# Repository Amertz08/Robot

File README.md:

# Senior design project

Repo for senior design

## Documentation

- [Contribution Guide](CONTRIBUTING.md)
- [Meeting notes](MEETING.md)

## Gantt Chart

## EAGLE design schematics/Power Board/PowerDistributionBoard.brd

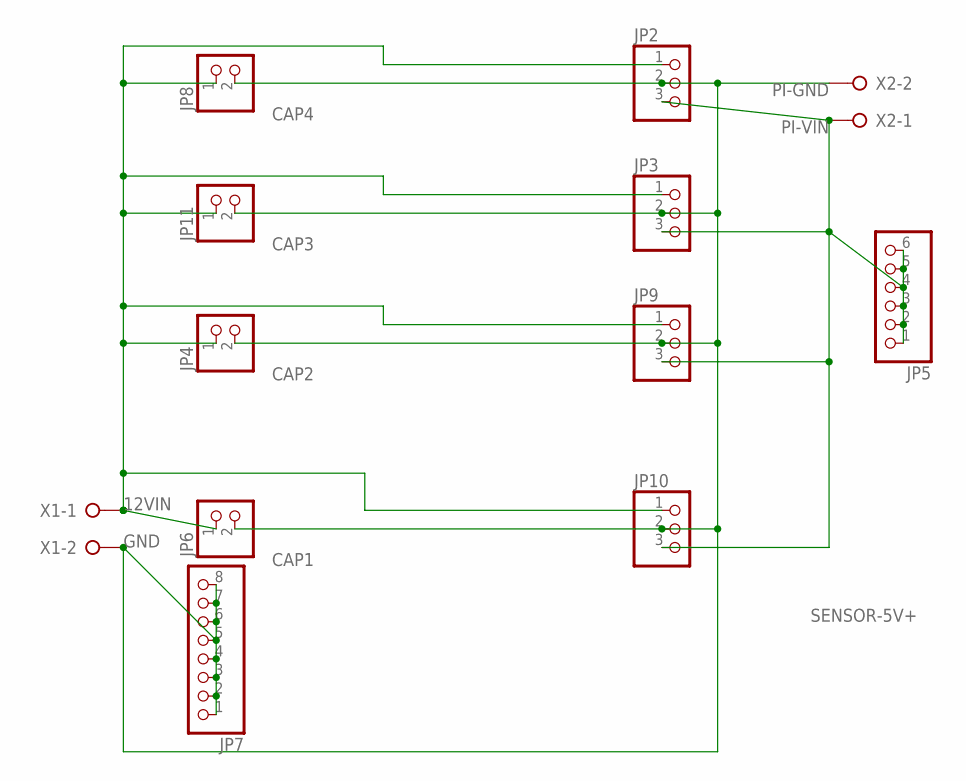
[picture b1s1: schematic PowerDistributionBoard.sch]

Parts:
JP2, JP3, JP9, JP10: PINHD-1X3; 1X03
JP4, JP6, JP8, JP11: PINHD-1X2; 1X02
JP5: PINHD-1X6; 1X06
JP7: PINHD-1X8; 1X08
X1, X2: W237-02P; W237-132

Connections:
COMMON-GND: JP2.2, JP3.2, JP4.2, JP6.2, JP7.1, JP7.2, JP7.3, JP7.4, JP7.5, JP7.6, JP7.7, JP7.8, JP8.2, JP9.2, JP10.2, JP11.2, X1.2, X2.2
unnamed: JP2.1, JP3.1, JP4.1, JP6.1, JP8.1, JP9.1, JP10.1, JP11.1, X1.1
SENSOR-5V+: JP2.3, JP3.3, JP5.1, JP5.2, JP5.3, JP5.4, JP5.5, JP5.6, JP9.3, JP10.3, X2.1

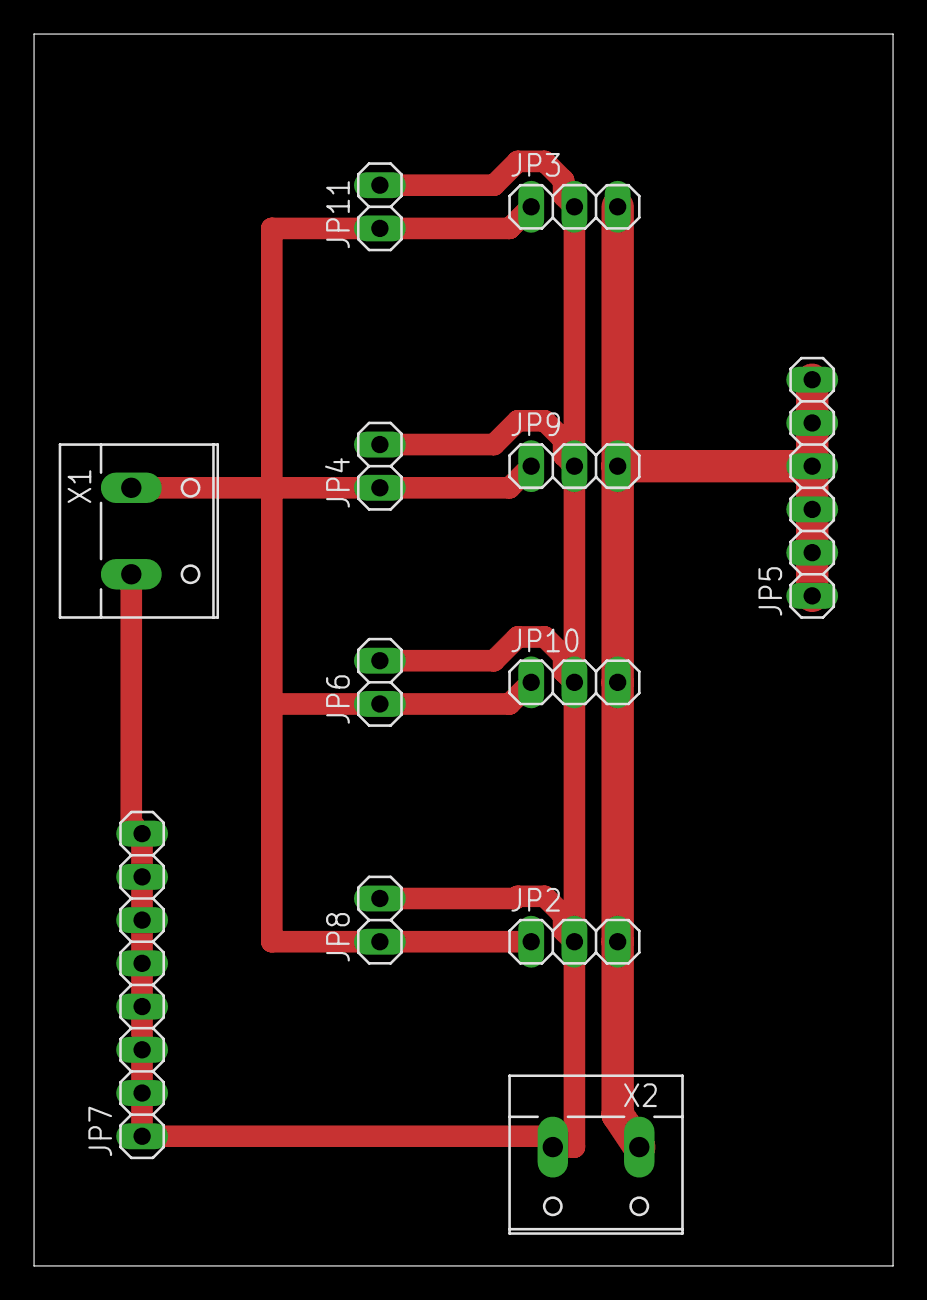
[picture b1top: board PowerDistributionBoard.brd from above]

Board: 2 copper layers, 50.5 x 72.4 mm, 12 parts (0 on the bottom side), 3 nets.

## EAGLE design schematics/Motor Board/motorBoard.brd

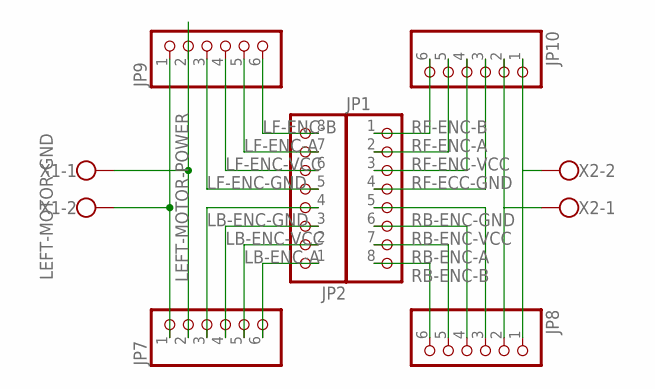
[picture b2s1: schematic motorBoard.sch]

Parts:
JP1, JP2: PINHD-1X8; 1X08
JP7, JP8, JP9, JP10: PINHD-1X6; 1X06
X1, X2: W237-102

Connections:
LB-ENC-A: JP2.2, JP7.5
LB-ENC-B: JP2.1, JP7.6
LB-ENC-GND: JP2.4, JP7.3
LB-ENC-VCC: JP2.3, JP7.4
LEFT-MOTOR-GND: JP7.2, JP9.2, X1.1
LEFT-MOTOR-POWER: JP7.1, JP9.1, X1.2
LF-ENC-A: JP2.7, JP9.5
LF-ENC-B: JP2.8, JP9.6
LF-ENC-GND: JP2.5, JP9.3
LF-ENC-VCC: JP2.6, JP9.4
unnamed: JP8.1, JP10.1, X2.2
unnamed: JP8.2, JP10.2, X2.1
RB-ENC-A: JP1.7, JP8.5
RB-ENC-B: JP1.8, JP8.6
RB-ENC-GND: JP1.5, JP8.3
RB-ENC-VCC: JP1.6, JP8.4
RF-ECC-GND: JP1.4, JP10.3
RF-ENC-A: JP1.2, JP10.5
RF-ENC-B: JP1.1, JP10.6
RF-ENC-VCC: JP1.3, JP10.4

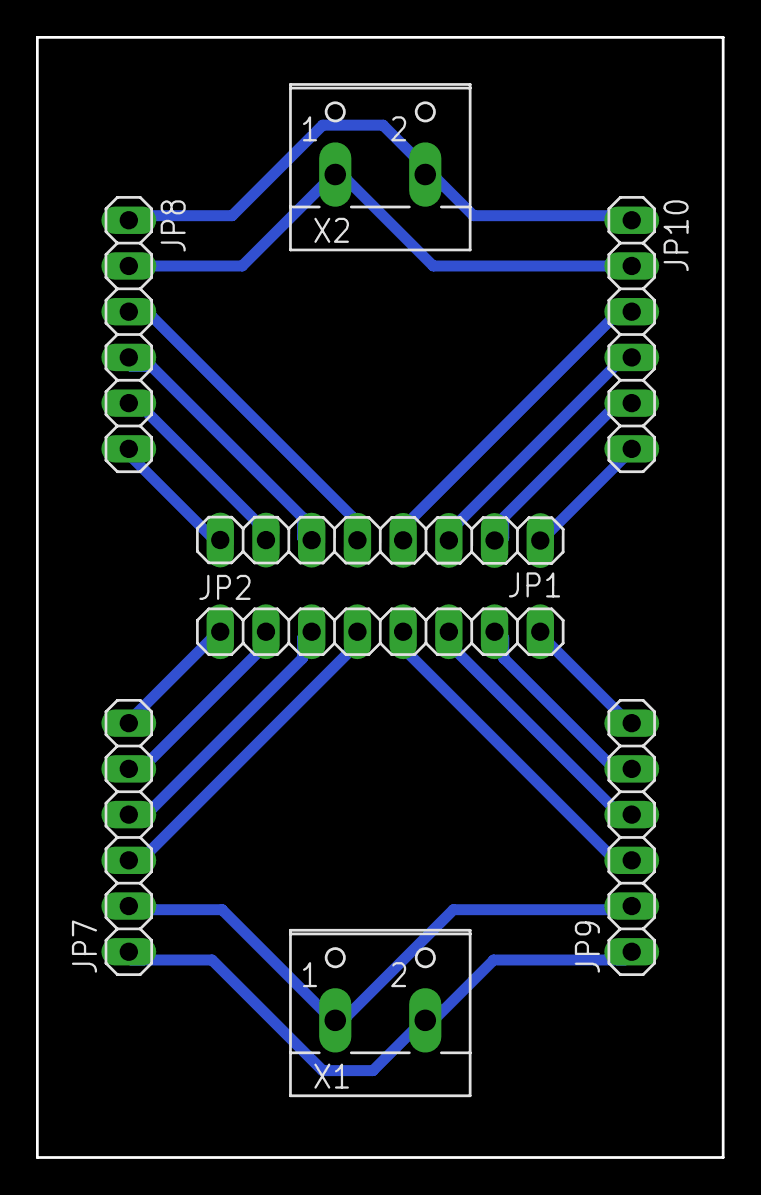
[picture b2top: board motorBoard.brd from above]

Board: 2 copper layers, 38.1 x 62.2 mm, 8 parts (0 on the bottom side), 20 nets.

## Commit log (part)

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2017-11-08 Created initial contribution guide.
2017-11-08 Noted that commits cannot be made to master. Added section on PR.
2017-11-08 Added note to include issue number on resolution
2017-11-27 Wrote basic READMEs for each of the directories for the codebases
2017-11-27 typo fix
2017-11-27 lowercase directory name
2018-01-18 Added script
2018-01-19 Added basic Makefile
2018-01-19 Updated README with environmental variables
2018-01-19 Added link to original script
2018-01-19 Cleaned up code
2018-01-19 Moved sketches to their own directory. Updated Makefile
2018-01-19 Moved command into its own variable
2018-01-19 Moved Makefile
2018-01-19 Updated Makefile with proper directories
2018-01-19 Updated clean target
2018-01-19 Started progress notes
2018-01-19 Added section for general notes
2018-01-19 Added missing envar
2018-01-19 Added name to separate sections
2018-01-19 Updated description/date
2018-01-19 Added part orders
2018-01-19 Added WIP section and changed notes to plans
2018-01-19 Bold to headings
2018-01-19 Add my progress, WIP and plan
2018-01-19 Another typo fix
2018-01-19 Added link in README to meeting note file
2018-01-20 Broker port envar
    Made broker port an environmental variable
2018-01-20 subscribe to all
    Changed subscription to all topics
2018-01-20 soft exit
    Added soft exit
2018-01-20 db write example
    Wrote basic db write example
2018-01-20 added logging
    Added basic file logger
2018-01-20 Updated log format
2018-01-20 fixed indent
2018-01-20 Added timestamp to test message
2018-01-20 Added my WIP and plans for the project.
2018-01-20 update README and CONTRIBUTING
2018-01-20 Fixed typo
    Fixed typo on commit
2018-01-20 updated issues
2018-01-20 syntax fixes
2018-01-20 add setup.py
2018-01-20 added Makefile targets
2018-01-21 added rm command to run
2018-01-24 Created simple sensor smoothing library
    calculates moving average of a user defined value for easier sensor
    reading.
2018-01-24 fixed spacing and newline at eof
2018-01-25 Added function to validate speed value
2018-01-25 Fixed max speed value
2018-01-25 Wrote deconstructor
2018-01-26 Rewrote example script logic as switch statement
2018-01-26 Updated header
2018-01-26 Refactored underlying motor pin writes to one function
2018-01-26 Added docstrings
2018-01-26 forgot to commit change
2018-01-26 Added methods to control motors for specific sides
2018-01-26 Add readCurrent method
2018-01-26 Added macros for encoder pins
    Added macros for encoder pins. converted ints to uint8_t
2018-01-26 Fixed type issues
2018-01-26 FIxed spacing issues
2018-01-26 Moved into routing directory
2018-01-26 Deleted extra lines
2018-01-26 Added example transformation
2018-01-26 Added notes
2018-01-26 Updated my details
    Here's what I did today.
2018-01-26 Add Dockerfile for basic flask app
2018-01-26 Add flask app which returns "Hello World"
2018-01-26 Add my changes
2018-01-26 Added issue closed by Collin.
2018-01-26 Gannt as a pdf
    converted jpg to pdf.
2018-01-26 Renamed files
2018-01-26 Fixed typos
2018-01-26 Created doc repo
2018-01-27 Moved documentation links to one header
2018-01-27 fixed typo strings
2018-01-30 Corrections to code/Yaml change
    Made massive changes to the code, and changed the configuration file to the YAML format.
2018-01-30 Final code revisions
    These are the changes for the most recent comments on the file.
2018-01-30 minor fixes
2018-01-30 Minor fixes
    graph must be explicitly defined as global in functions that want to change it. Added function docstrings. Converted while to for loop. Minor typo fix
2018-01-30 Fixes
    Made certain methods properties. PEP8 style fixes. Default empty list param cannot be declared in function def
2018-01-30 missed reserved word variable naming
    Previously removed reserved word usage. Forgot this one
2018-01-30 Add web service to docker compose file
2018-01-30 Change port exposed to 5000, and change Flask version to 0.12.0
2018-01-30 Commented out exceptions
    Arduino does not allow exceptions. Commented out in order to compile for now.
2018-02-01 basic keyboard script
2018-02-01 Added soft exit on script
2018-02-01 printed valid nodes on invalid node input
2018-02-02 Created base template that integrates bootstrap
2018-02-02 renamed file extension
2018-02-02 Minor fixes
    File extension fix. Added templates folder to Dockerfile
2018-02-02 Added meeting notes
2018-02-02 Integrate i2c into previous line array code
2018-02-02 minor changes
2018-02-02 Minor changes and additions
2018-02-02 Added my progress and plans
2018-02-06 Moved main index.html under sub folder
2018-02-06 Formatting
2018-02-09 Added stop on obstacle detection
    Using the ultrasonic sensor we can detect obstacles in the way of the
    robot and stop
2018-02-10 Added my Notes
2018-02-10 Added sparkfun line follower library
2018-02-11 My weekly changes
2018-02-13 Changes to app.py
2018-02-16 Moved docstrings
2018-02-19 Update MEETING.md
    We didn't do this last week.
2018-02-19 Fixed issue number
2018-02-21 My changes
2018-02-23 Create models
2018-02-25 Started command app
2018-02-26 Update MEETING.md
    My changes
2018-02-27 Minor changes to config
    Removed unnecessary definitions in base config object. Self reference was incorrect.
2018-02-27 Added targets for logs on web application
2018-02-27 Started blueprint
2018-02-27 Created basic form and view
2018-02-27 Added UserMixin to User model
2018-02-27 removed whitespace
2018-02-27 Integrated login manager
2018-02-27 Added target to run bash in web container
2018-02-27 Properly init sqlalchemy instance
2018-02-27 Created defaults for user model
    Removed unnecessary parameters from constructor. Defined defaults on appropriate columns.
2018-02-27 set_password should be staticmethod
2018-02-27 Fixed missing imports
2018-02-27 Created basic CLI app
2018-02-27 Added Directional Support/Efficient Route selection
    Added a dictionary to the file that creates values of the direction to travel given the key of a pair of nodes. I also added efficient route selection which simply selects the shortest path to travel.
2018-02-27 Docker for route solver
    This is the docker I created for the Route Solver. The CMD line does not contain all arguments because they vary based on the route you wish to solve. Not including them allows for user prompt.
2018-03-01 started template
2018-03-01 PEP8 Spacing
2018-03-02 Implement sign up route
2018-03-02 Link to sign up page
2018-03-02 missed one
2018-03-02 Add validator max length
2018-03-02 Use acct variable instead of User model
2018-03-02 Add my change
2018-03-02 My changes added
2018-03-02 Login user on registration, fix session commit.
2018-03-03 My progress
2018-03-06 Confirmation route
2018-03-06 Add flask mail
2018-03-08 Add validation route
2018-03-08 Add 404 page
2018-03-08 Commit to database
2018-03-08 Add resend email function
2018-03-08 User need to confirm to access site
2018-03-08 Add print url if debug is true
2018-03-08 intial working example
2018-03-08 Run python unbuffered
2018-03-08 Fixed home link in navbar
2018-03-08 Updated models repr
2018-03-08 Added relationship properties to models
2018-03-09 Moved db commit to actual reset method
2018-03-09 Got basic pytest to work
2018-03-09 Function to print messages if app is in debug mode
2018-03-09 Removed pytest
2018-03-09 Started auth tests
2018-03-09 Change sendemail to util
2018-03-09 Add verified date
2018-03-09 Changes, add confirm.html
2018-03-09 Add confirm.html
2018-03-09 white space
2018-03-09 Serialized User.id and not User.acct_id
2018-03-10 Only send emails async when not in debug mode so errors can be seen
2018-03-10 Added SMTP settings to config
2018-03-10 User model must be committed before token generation
2018-03-10 Redirect to index on success
2018-03-10 Added link in flash message to resend verification email
2018-03-10 Added handler for 404 errors
2018-03-10 Created Meeting Minutes Update
    Added my changes
2018-03-10 Spacing fixes
    General fixes
2018-03-13 Used print_debug function for views
2018-03-13 Wrote wrapper function to get User model by email
2018-03-13 Created reset password template and implemented sending of email
2018-03-13 Renamed file to test only routes
2018-03-13 Added test for unverified message on login
2018-03-13 Expanded test cases
2018-03-13 Expired token test
2018-03-13 Added makefile target for routes
2018-03-15 Removed confirm method and moved logic into view. Fixed #98
2018-03-15 Remove replicated code
2018-03-15 Added this week with my changes
2018-03-15 Created helper function to log messages
2018-03-15 Added log format and handler for file logging
2018-03-15 Docker volume for logs
2018-03-15 Added log messages to app
2018-03-16 Proper mapping of db for persistent data
2018-03-16 unused import
2018-03-16 init_app should be static method
2018-03-16 My notes
2018-03-27 Fixed logging bad import
2018-03-27 Added dash.index view
2018-03-27 Added simple heading to dash index
2018-03-29 Navbar link to dashboard index
2018-03-29 Basic relationships
2018-03-29 Sign up route test
2018-03-30 Confirm route test
2018-03-30 Confirm route token test
2018-04-02 Add user form, route, template
2018-04-02 Add SQL target
2018-04-02 Fixed log message issue
2018-04-02 Removed print statements
2018-04-03 Test for add user route
2018-04-03 Add validation on account
2018-04-03 Test route for add user with invalid company
2018-04-03 Remove user template, form, route
2018-04-03 Remove user test routes
2018-04-04 AddFacilityForm
2018-04-04 Added facilities table. Add/Edit facility modals
2018-04-04 Update/DeleteFacilityForms
2018-04-04 partially working JS to handle modals and form submissions
2018-04-04 Actually submit update form
2018-04-04 Close edit modal
2018-04-04 Print app config level
2018-04-04 Dynamic post URLs
2018-04-04 Constructor for Facility
2018-04-04 Started TestDash test cases
2018-04-05 double quotes
2018-04-05 Removed conflict
2018-04-05 fixed delay issues
2018-04-05 Test error message responses
2018-04-05 Started basic layouts route
2018-04-05 Added URL parameter to show layouts for specific facility
2018-04-05 Invalid facility_id on layouts test case
2018-04-05 Started AddLayoutsForm
2018-04-05 Remove errors and text on dismiss
2018-04-05 Refactored help message append into function
2018-04-05 Refactored addHelp function into it's own JS file
2018-04-05 Refactored removeHelp function
2018-04-06 Close add facility monitor. Added listener to proper buttons.
2018-04-06 Fixed dismissal close button not resetting form.
2018-04-06 Added ability to suppress send with environemental variable
2018-04-06 Resolves #107
2018-04-06 Validation for connections
2018-04-06 Set password template
2018-04-06 Fix template
2018-04-06 Fix template url
2018-04-06 Test cases for new add user route
2018-04-06 Change remove user route and form
2018-04-06 Test cases for remove user
2018-04-06 Setting up for communicating with Pi
2018-04-06 Started Pi/Arduino communication
2018-04-06 working on determining next direction
2018-04-10 move callback
2018-04-10 Allow sensor arduino to take instructions from RPi
2018-04-10 fix delay times
2018-04-11 Changes to run the pi comms throughout the route
    Several changes in this commit:
    Moved all files to the /pi/ directory for ease of import
    Created a new route_solver.py file that is a condensed version of the original command line driven one. (Still uses yaml #TODO)
    updated the pi_I2c file to take in the map, and end node from the server comms and start the driving/continue along the route through to finish.
2018-04-12 Remove test files
2018-04-12 Properly reset add-layout form
2018-04-17 Uploaded All EAGLE files
    Main Power Board (Sensor Board) and the Motor Board
2018-04-17 Rearranged directories
    Also uploaded final version of PCB
2018-04-17 Final Board Sent for Fabrication
2018-04-24 Change add and remove user view function
2018-04-24 Remove add & remove user template
2018-04-24 Add account management template
2018-04-24 Change remove user flash message to danger
2018-04-27 added working arduino code
2018-04-29 Created poster
2018-05-11 updated turning
